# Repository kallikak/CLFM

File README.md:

# CLFM
Cherchez la FM - 4 operator Eurorack voice

See the build guide http://thewessens.net/CLFM/CLFMbuild.html for more information.

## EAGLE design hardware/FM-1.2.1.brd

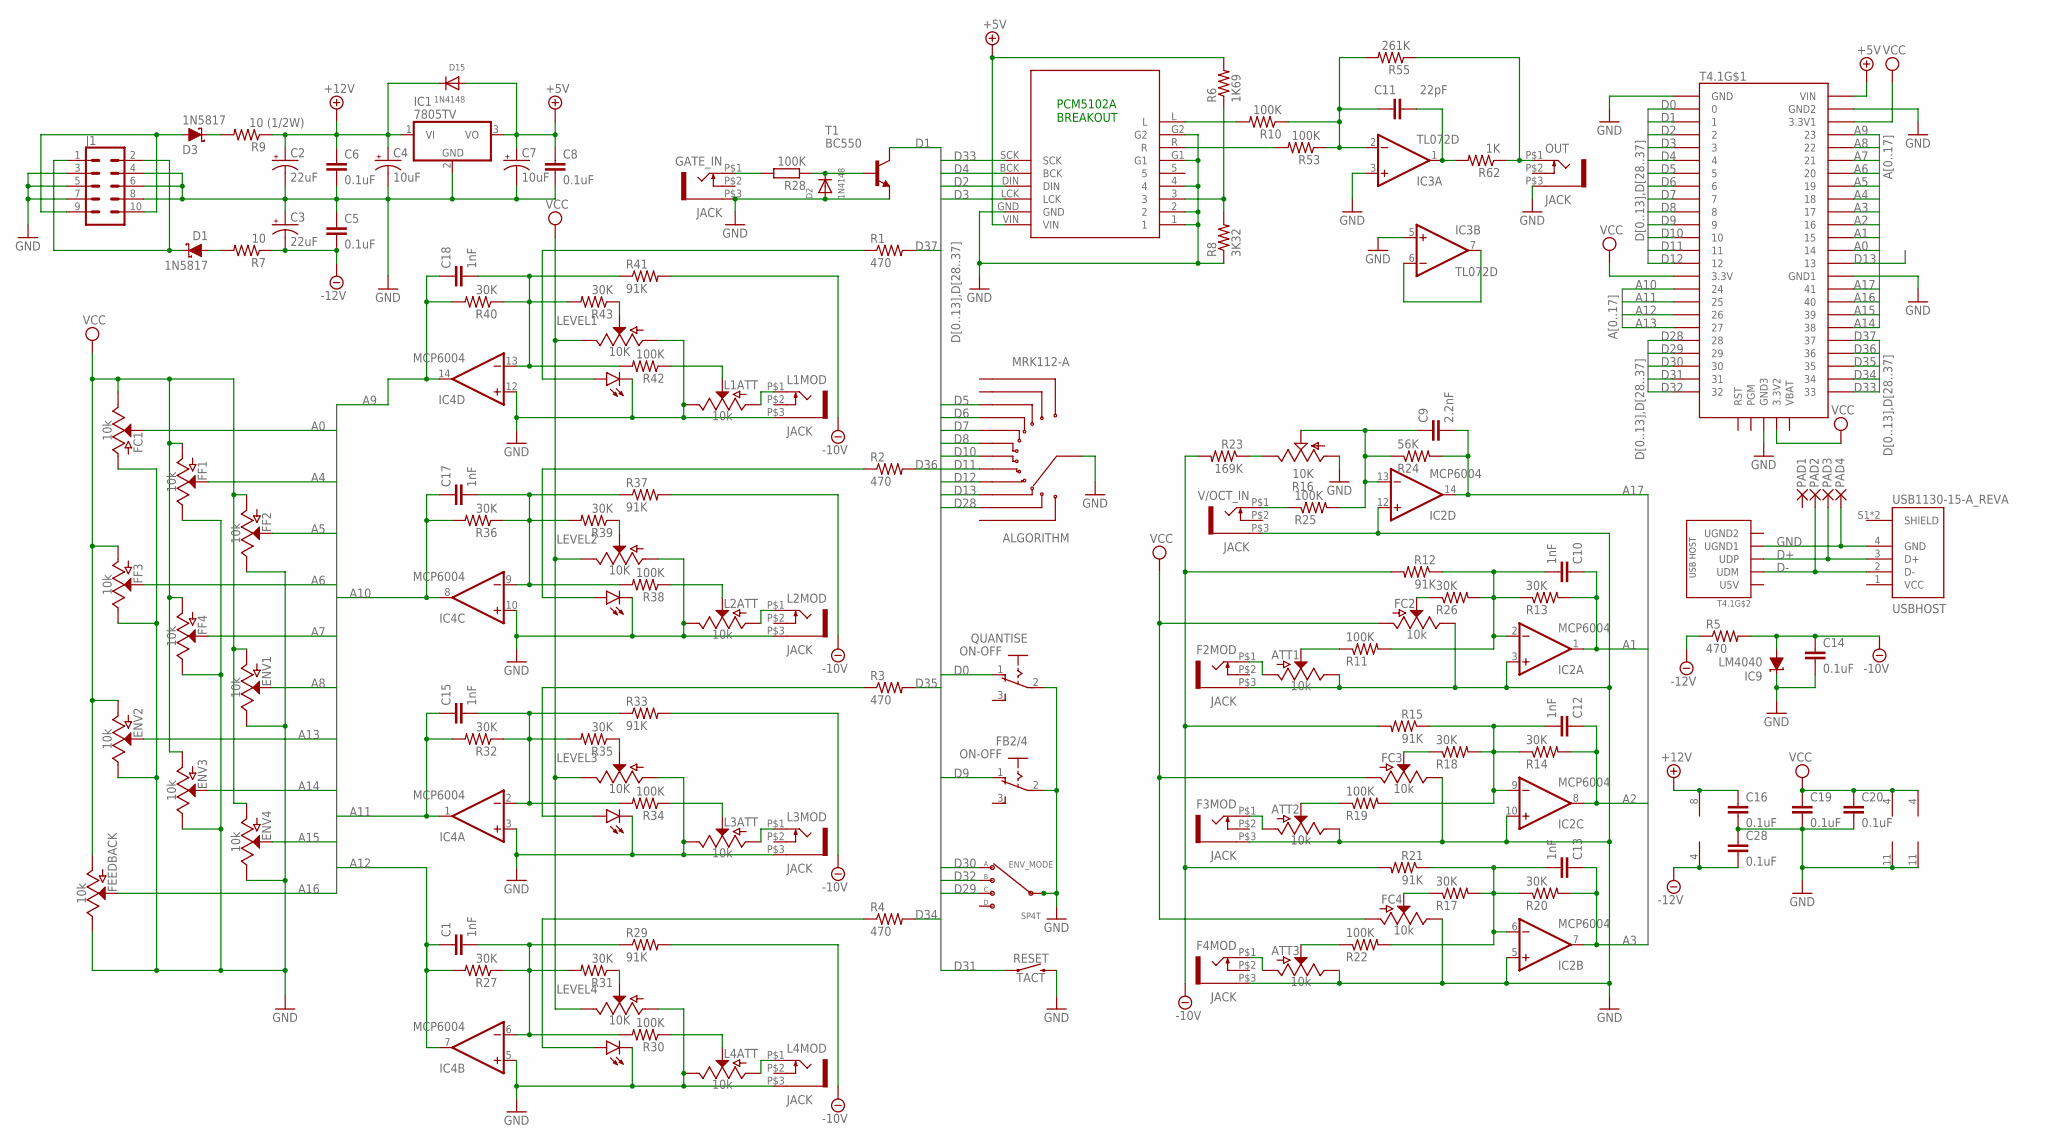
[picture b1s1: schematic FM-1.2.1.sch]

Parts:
ALGORITHM: MRK112-A; SW_MRK112-A
ATT1, ATT2, ATT3: 10k; POT-PTH-ALPS
C1, C10, C12, C13, C15, C17, C18: 1nF; C0603K
C2, C3: 22uF; CPOL-RADIAL-2.5MM-5MM
C4, C7: 10uF; CPOL-RADIAL-2.5MM-5MM
C5, C6, C8, C14, C16, C19, C20, C28: 0.1uF; C0603K
C9: 2.2nF; C0603K
C11: 22pF; C0603K
D1, D3: 1N5817; SOD-323
D2, D15: 1N4148; SOD-123
ENV1, ENV2, ENV3, ENV4: 10k; POT-PTH-ALPS
ENV_MODE: SP4T
F2MOD, F3MOD, F4MOD: JACK; WQP-PJ301M-12_JACK
FB2/4: ON-OFF; 255SB
FC1, FC2, FC3, FC4: 10k; POT-PTH-ALPS
FEEDBACK: 10k; POT-PTH-ALPS
FF1, FF2, FF3, FF4: 10k; POT-PTH-ALPS
GATE_IN: JACK; WQP-PJ301M-12_JACK
IC1: 7805TV; TO220V
IC2, IC4: MCP6004; SO14
IC3: TL072D; SO08
IC9: LM4040; LP_O-PBCY-W3
J1: CONN_05X2SHD; 2X5-SHROUDED
L1ATT, L2ATT, L3ATT, L4ATT: 10k; POT-PTH-ALPS
L1MOD, L2MOD, L3MOD, L4MOD: JACK; WQP-PJ301M-12_JACK
LEVEL1, LEVEL2, LEVEL3, LEVEL4: 10K; SLIDER-MEDIUM-LED
OUT: JACK; WQP-PJ301M-12_JACK
PAD1, PAD2, PAD3, PAD4: 1,6/0,9
QUANTISE: ON-OFF; 255SB
R1, R2, R3, R4, R5: 470; R0603
R6: 1K69; R0603
R7: 10; R0603
R8: 3K32; R0603
R9: 10 (1/2W); 0207/10
R10, R11, R19, R22, R25, R28, R30, R34, R38, R42, R53: 100K; R0603
R12, R15, R21, R29, R33, R37, R41: 91K; R0603
R13, R14, R17, R18, R20, R26, R27, R31, R32, R35, R36, R39, R40, R43: 30K; R0603
R16: 10K; B25P
R23: 169K; R0603
R24: 56K; R0603
R55: 261K; R0603
R62: 1K; R0603
RESET: TACT; TACTILE_SWITCH_PTH_6.0MM
T1: BC550; TO92
T4.1: TEENSY4.1
U$2: PCM5102A BREAKOUT; I2S_PCM_5100_SOUNDCARD
USBHOST: USB1130-15-A_REVA; GCT_USB1130-15-A_REVA
V/OCT_IN: JACK; WQP-PJ301M-12_JACK

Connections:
+5V: C7.1 (+), C8.1, D15.A, IC1.3 (VO), R6.2, T4.1.VIN, U$2.VIN
+12V: C2.1 (+), C4.1 (+), C6.1, C16.1, D15.C, IC1.1 (VI), IC3.8 (V+), R9.1
-10V: C14.1, IC9.3 (A), R5.2, R12.2, R15.2, R21.2, R23.2, R29.2, R33.2, R37.2, R41.2
-12V: C3.2 (-), C5.2, C28.2, IC3.4 (V-), R5.1, R7.1
A0: FC1.P$2 (S), T4.1.14/A0 (14)
A1: C10.1, IC2.1 (OUT), R13.2, T4.1.15/A1 (15)
A2: C12.1, IC2.8 (OUT), R14.2, T4.1.16/A2 (16)
A3: C13.1, IC2.7 (OUT), R20.2, T4.1.17/A3 (17)
A4: FF1.P$2 (S), T4.1.18/A4/SDA (18)
A5: FF2.P$2 (S), T4.1.19/A5/SCL (19)
A6: FF3.P$2 (S), T4.1.20/A6 (20)
A7: FF4.P$2 (S), T4.1.21/A7 (21)
A8: ENV1.P$2 (S), T4.1.22/A8 (22)
A9: C18.1, IC4.14 (OUT), R40.2, T4.1.23/A9 (23)
A10: C17.1, IC4.8 (OUT), R36.2, T4.1.24
A11: C15.1, IC4.1 (OUT), R32.2, T4.1.25
A12: C1.1, IC4.7 (OUT), R27.2, T4.1.26
A13: ENV2.P$2 (S), T4.1.27
A14: ENV3.P$2 (S), T4.1.38
A15: ENV4.P$2 (S), T4.1.39
A16: FEEDBACK.P$2 (S), T4.1.40
A17: C9.2, IC2.14 (OUT), R24.2, T4.1.41
D0: QUANTISE.1 (O), T4.1.0/RX (0)
D1: T1.3 (C), T4.1.1/TX (1)
D2: T4.1.2, U$2.DIN
D3: T4.1.3, U$2.LCK
D4: T4.1.4, U$2.BCK
D5: ALGORITHM.10, T4.1.5
D6: ALGORITHM.9, T4.1.6
D7: ALGORITHM.8, T4.1.7
D8: ALGORITHM.7, T4.1.8
D9: FB2/4.1 (O), T4.1.9
D10: ALGORITHM.6, T4.1.10/CS (10)
D11: ALGORITHM.5, T4.1.11/MOSI (11)
D12: ALGORITHM.4, T4.1.12/MISO (12)
D13: ALGORITHM.3, T4.1.13/SCK (13)
D28: ALGORITHM.2, T4.1.28
D29: ENV_MODE.4 (C), T4.1.29
D30: ENV_MODE.2 (A), T4.1.30
D31: RESET.1, T4.1.31/A12 (31)
D32: ENV_MODE.3 (B), T4.1.32
D33: T4.1.33, U$2.SCK
D34: R4.2, T4.1.34
D35: R3.2, T4.1.35
D36: R2.2, T4.1.36
D37: R1.2, T4.1.37
D+: PAD3.1, T4.1.UD+ (UDP), USBHOST.3 (D+)
D-: PAD2.1, T4.1.UD- (UDM), USBHOST.2 (D-)
GND: ALGORITHM.A, ATT1.P$1 (E), ATT2.P$1 (E), ATT3.P$1 (E), C2.2 (-), C3.1 (+), C4.2 (-), C5.1, C6.2, C7.2 (-), C8.2, C14.2, C16.2, C19.2, C20.2, C28.1, D2.A, ENV1.P$1 (E), ENV2.P$1 (E), ENV3.P$1 (E), ENV4.P$1 (E), ENV_MODE.1 (INPUT), ENV_MODE.6, F2MOD.P$3 (1), F3MOD.P$3 (1), F4MOD.P$3 (1), FB2/4.2, FC1.P$3 (A), FC2.P$1 (E), FC3.P$1 (E), FC4.P$1 (E), FEEDBACK.P$1 (E), FF1.P$1 (E), FF2.P$1 (E), FF3.P$1 (E), FF4.P$1 (E), GATE_IN.P$3 (1), IC1.2 (GND), IC2.3 (+IN), IC2.5 (+IN), IC2.10 (+IN), IC2.11 (V-), IC2.12 (+IN), IC3.3 (+IN), IC3.5 (+IN), IC4.3 (+IN), IC4.5 (+IN), IC4.10 (+IN), IC4.11 (V-), IC4.12 (+IN), IC9.2 (C), J1.3, J1.4, J1.5, J1.6, J1.7, J1.8, L1ATT.P$1 (E), L1MOD.P$3 (1), L2ATT.P$1 (E), L2MOD.P$3 (1), L3ATT.P$1 (E), L3MOD.P$3 (1), L4ATT.P$1 (E), L4MOD.P$3 (1), LEVEL1.P$1 (1), LEVEL1.P$E (E), LEVEL2.P$1 (1), LEVEL2.P$E (E), LEVEL3.P$1 (1), LEVEL3.P$E (E), LEVEL4.P$1 (1), LEVEL4.P$E (E), OUT.P$3 (1), PAD4.1, QUANTISE.2, R8.1, R16.A, RESET.3 (2), T1.1 (E), T4.1.AGND (GND2), T4.1.GND, T4.1.GND1, T4.1.GND2 (GND3), T4.1.GND-U1 (UGND1), U$2.1, U$2.2, U$2.4, U$2.G1, U$2.G2, U$2.GND, USBHOST.4 (GND), V/OCT_IN.P$3 (1)
unnamed: C11.2, IC3.1 (OUT), R62.2
unnamed: LEVEL3.P$B (B), R3.1
unnamed: C15.2, IC4.2 (-IN), R32.1, R33.1, R34.2, R35.2
unnamed: D1.C, J1.1, J1.2
unnamed: R25.1, V/OCT_IN.P$1 (2)
unnamed: D3.A, J1.9, J1.10
unnamed: D3.C, R9.2
unnamed: LEVEL3.P$2 (2), R35.1
unnamed: D1.A, R7.2
unnamed: LEVEL4.P$B (B), R4.1
unnamed: R10.2, U$2.L
unnamed: R6.1, R8.2, U$2.3
unnamed: R53.2, U$2.R
unnamed: ATT2.P$3 (A), F3MOD.P$1 (2)
unnamed: FC2.P$2 (S), R26.1
unnamed: C10.2, IC2.2 (-IN), R11.2, R12.1, R13.1, R26.2
unnamed: C12.2, IC2.9 (-IN), R14.1, R15.1, R18.2, R19.2
unnamed: ATT1.P$2 (S), R11.1
unnamed: C13.2, IC2.6 (-IN), R17.2, R20.1, R21.1, R22.2
unnamed: ATT2.P$2 (S), R19.1
unnamed: C9.1, IC2.13 (-IN), R16.S, R24.1, R25.2
unnamed: FC4.P$2 (S), R17.1
unnamed: ATT3.P$3 (A), F4MOD.P$1 (2)
unnamed: FC3.P$2 (S), R18.1
unnamed: R16.E, R23.1
unnamed: IC3.6 (-IN), IC3.7 (OUT)
unnamed: ATT3.P$2 (S), R22.1
unnamed: ATT1.P$3 (A), F2MOD.P$1 (2)
unnamed: GATE_IN.P$1 (2), R28.2
unnamed: D2.C, R28.1, T1.2 (B)
unnamed: C1.2, IC4.6 (-IN), R27.1, R29.1, R30.2, R31.2
unnamed: LEVEL4.P$2 (2), R31.1
unnamed: L4ATT.P$3 (A), L4MOD.P$1 (2)
unnamed: L4ATT.P$2 (S), R30.1
unnamed: L3ATT.P$3 (A), L3MOD.P$1 (2)
unnamed: L3ATT.P$2 (S), R34.1
unnamed: LEVEL2.P$B (B), R2.1
unnamed: C17.2, IC4.9 (-IN), R36.1, R37.1, R38.2, R39.2
unnamed: LEVEL2.P$2 (2), R39.1
unnamed: L2ATT.P$3 (A), L2MOD.P$1 (2)
unnamed: L2ATT.P$2 (S), R38.1
unnamed: LEVEL1.P$B (B), R1.1
unnamed: C18.2, IC4.13 (-IN), R40.1, R41.1, R42.2, R43.2
unnamed: LEVEL1.P$2 (2), R43.1
unnamed: L1ATT.P$3 (A), L1MOD.P$1 (2)
unnamed: L1ATT.P$2 (S), R42.1
unnamed: C11.1, IC3.2 (-IN), R10.1, R53.1, R55.2
unnamed: OUT.P$1 (2), R55.1, R62.1
VCC: C19.1, C20.1, ENV1.P$3 (A), ENV2.P$3 (A), ENV3.P$3 (A), ENV4.P$3 (A), FC1.P$1 (E), FC2.P$3 (A), FC3.P$3 (A), FC4.P$3 (A), FEEDBACK.P$3 (A), FF1.P$3 (A), FF2.P$3 (A), FF3.P$3 (A), FF4.P$3 (A), IC2.4 (V+), IC4.4 (V+), LEVEL1.P$3 (3), LEVEL2.P$3 (3), LEVEL3.P$3 (3), LEVEL4.P$3 (3), T4.1.3V3 (3.3V), T4.1.3V3_LO (3.3V1), T4.1.V33 (3.3V2), USBHOST.1 (VCC)

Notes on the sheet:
PCM5102A BREAKOUT

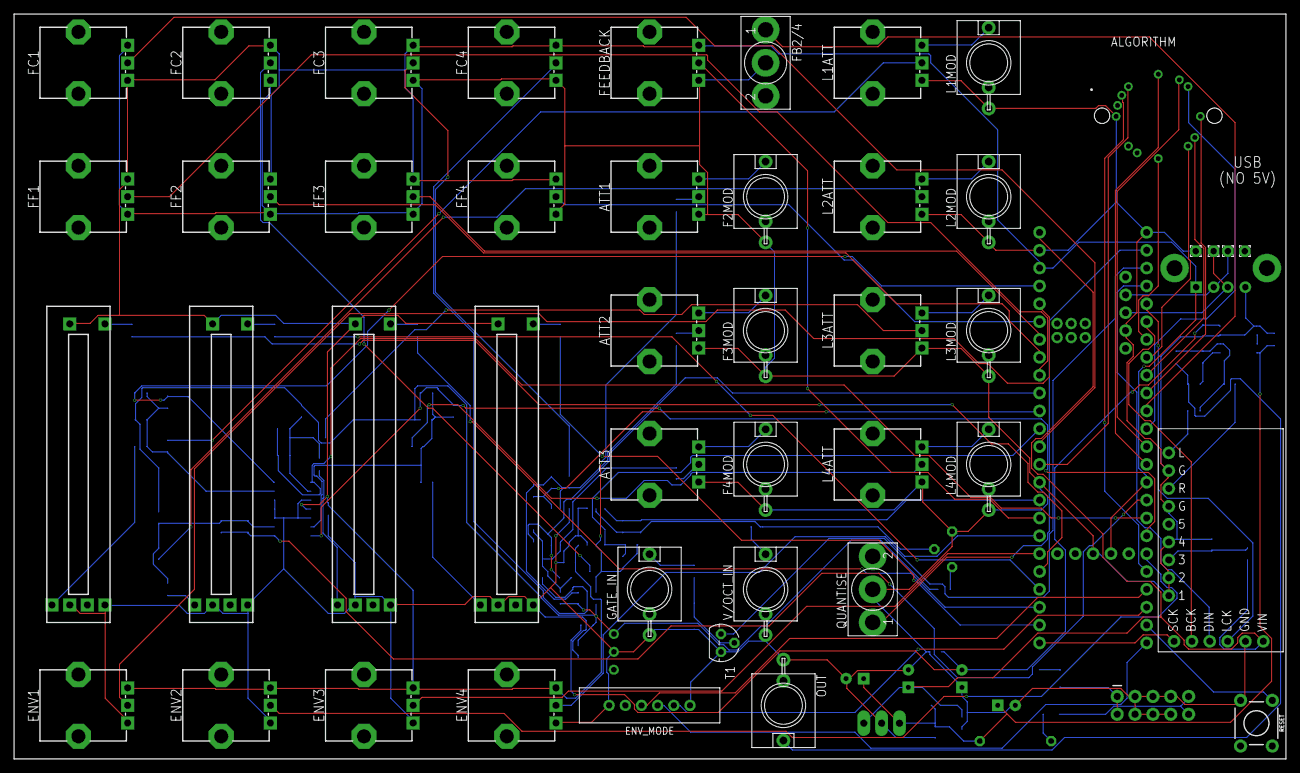
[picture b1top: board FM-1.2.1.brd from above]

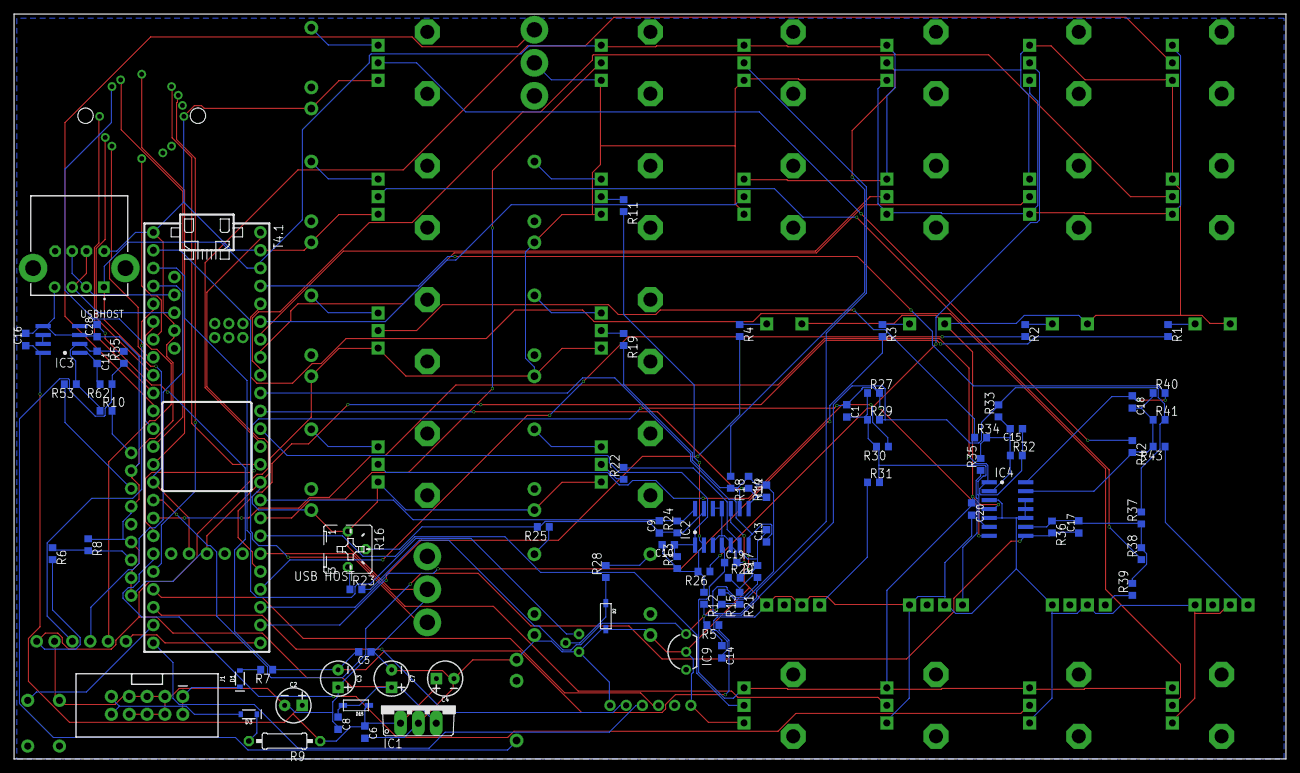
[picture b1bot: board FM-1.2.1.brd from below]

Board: 2 copper layers, 181.0 x 106.0 mm, 124 parts (79 on the bottom side), 98 nets.

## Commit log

2022-06-24 Panel image
2022-06-26 Polyphony via USB MIDI. Changed detune behaviour.
2022-06-26 Removed some logging
2022-06-26 Update CLFM-dexed.ino
    Fixed a startup glitch
2022-06-27 Fix for FB-2 algorithm inbus
2022-06-27 poly levels and osc sync
2022-06-27 increased polyphony to 16 notes
2022-06-29 mod wheel and aftertouch control of modulation
2022-06-29 Improved mod wheel and aftertouch scaling
2022-06-29 osc sync control
2022-07-09 Much improved operator 2 feedback algorithms
    Significant update to firmware - wavefolding and other waveforms added to selected alternate algorithms
2022-07-09 Removed special case folded wave code
2022-07-09 Smoother feedback response
2022-07-24 Removed prototype code
2022-07-25 Added part to BOM
2022-08-16 Improved feedback and optional square wave for negative
2022-08-25 Coarse multiples now up to 16 with additional divisors

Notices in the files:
parts and their libraries:
SparkFun-Switches: Licensing: Creative Commons ShareAlike 4.0 International - https://creativecommons.org/licenses/by-sa/4.0
